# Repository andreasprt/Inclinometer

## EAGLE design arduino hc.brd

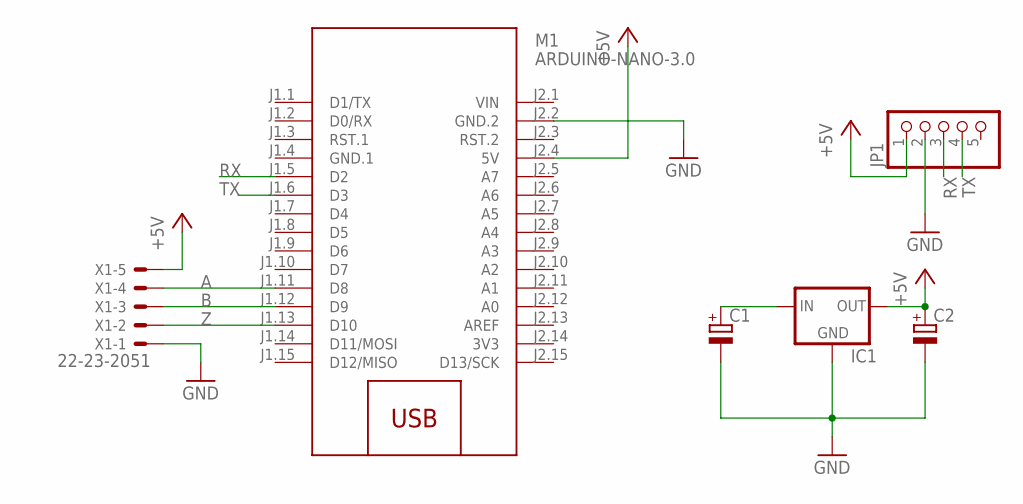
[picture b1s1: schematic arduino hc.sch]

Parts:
C1, C2: CPOL-EUE2,5-6E; E2,5-6E
IC1: 78XXS
JP1: PINHD-1X5; 1X05
M1: ARDUINO-NANO-3.0
X1: 22-23-2051

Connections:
3V3: M1.J2.14 (3V3)
+5V: C2.+, IC1.OUT, JP1.1, M1.J2.4 (5V), X1.5
A: M1.J1.11 (D8), X1.4
B: M1.J1.12 (D9), X1.3
GND: C1.-, C2.-, IC1.GND, JP1.2, M1.J2.2 (GND.2), X1.1
GND.1: M1.J1.4 (GND.1)
RX: JP1.3, M1.J1.5 (D2)
TX: JP1.4, M1.J1.6 (D3)
VCC: C1.+, IC1.IN
VIN: M1.J2.1 (VIN)
Z: M1.J1.13 (D10), X1.2

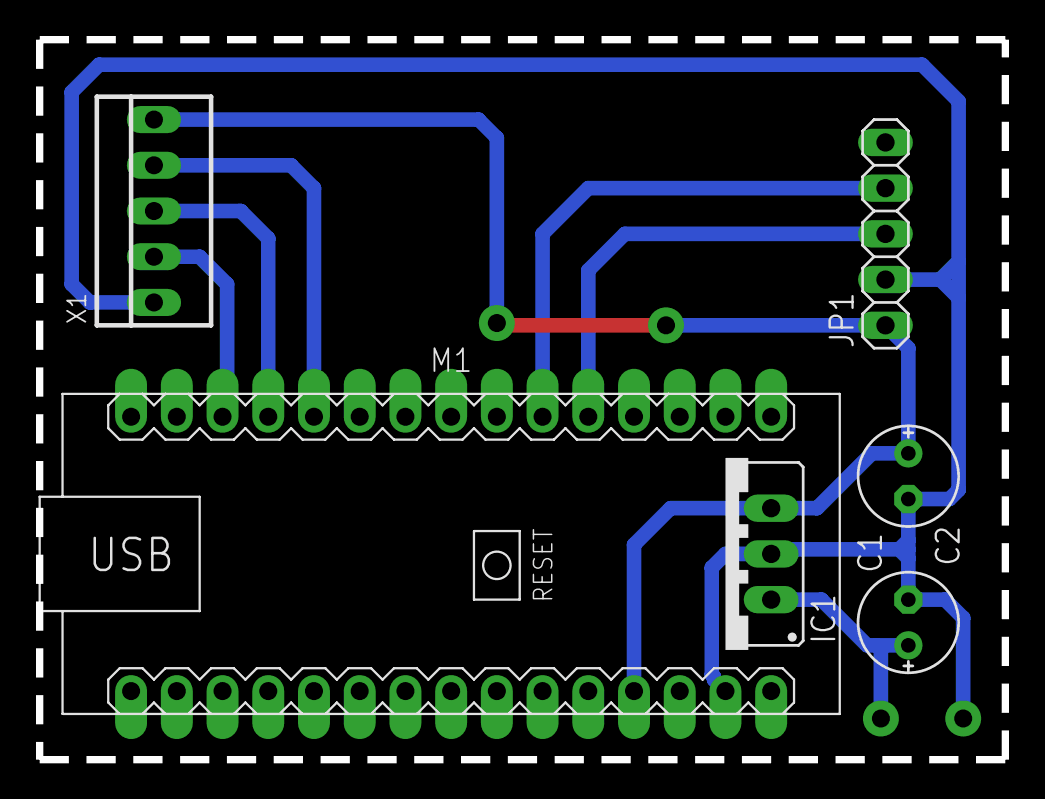
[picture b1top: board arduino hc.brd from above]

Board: 2 copper layers, 53.6 x 40.0 mm, 6 parts (0 on the bottom side), 8 nets.

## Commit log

2021-08-29 menambah file ino
2021-08-29 mengubah program
2021-10-12 tambah program master slave dan bluetooth
2021-10-27 update program master slave dan pcb
2021-10-27 new arduino encoder hc12
2021-11-01 tambah windows form
2021-11-08 update atmega2560
2021-11-08 update Gui

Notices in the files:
parts and their libraries:
diy-modules: Released under the Creative Commons Attribution 4.0 International License: http://creativecommons.org/licenses/by/4.0
